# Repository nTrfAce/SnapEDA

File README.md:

# SnapEDA

See also https://oshpark.com/profiles/nTrfAce for links to order the boards, images of them, and suggestions on connector part numbers.

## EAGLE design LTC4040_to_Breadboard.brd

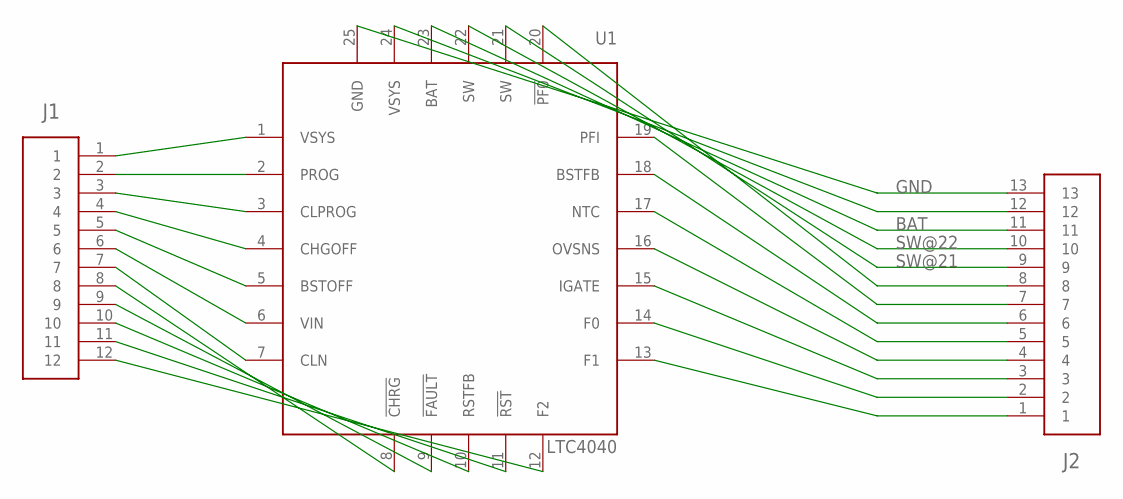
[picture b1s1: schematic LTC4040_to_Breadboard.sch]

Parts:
J1: CONNECTOR_12; 68000-112HLF
J2: CONNECTOR_13; 68000-113HLF_NO_SQUARE
U1: LTC4040; QFN50P500X400X80-25N

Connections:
BAT: J2.11, U1.23 (BAT)
GND: J2.13, U1.25 (GND)
unnamed: J1.1, U1.1 (VSYS)
unnamed: J1.2, U1.2 (PROG)
unnamed: J1.3, U1.3 (CLPROG)
unnamed: J1.4, U1.4 (CHGOFF)
unnamed: J1.5, U1.5 (BSTOFF)
unnamed: J1.6, U1.6 (VIN)
unnamed: J1.7, U1.7 (CLN)
unnamed: J1.8, U1.8 (!CHRG)
unnamed: J1.9, U1.9 (!FAULT)
unnamed: J1.10, U1.10 (RSTFB)
unnamed: J1.11, U1.11 (!RST)
unnamed: J1.12, U1.12 (F2)
unnamed: J2.1, U1.13 (F1)
unnamed: J2.2, U1.14 (F0)
unnamed: J2.3, U1.15 (IGATE)
unnamed: J2.4, U1.16 (OVSNS)
unnamed: J2.5, U1.17 (NTC)
unnamed: J2.6, U1.18 (BSTFB)
unnamed: J2.7, U1.19 (PFI)
unnamed: J2.8, U1.20 (!PF0)
unnamed: J2.12, U1.24 (VSYS)
SW@21: J2.9, U1.21 (SW)
SW@22: J2.10, U1.22 (SW)

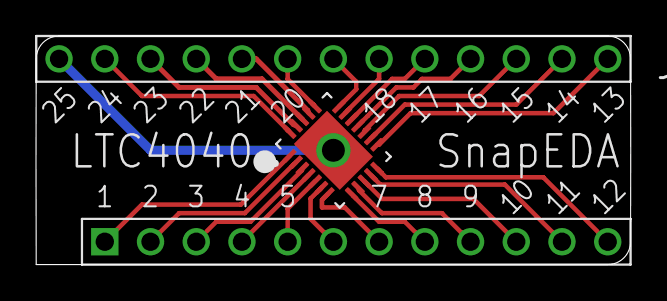
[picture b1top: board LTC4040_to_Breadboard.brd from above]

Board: 2 copper layers, 33.0 x 12.7 mm, 3 parts (0 on the bottom side), 25 nets.

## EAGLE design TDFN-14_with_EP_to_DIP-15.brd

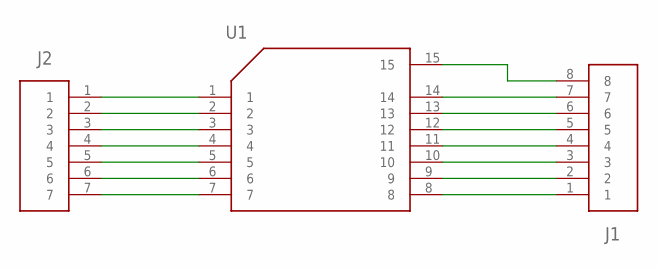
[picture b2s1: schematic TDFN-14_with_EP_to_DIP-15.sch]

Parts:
J1: CONNECTOR_8-NO_SQUARE; 68000-108HLF-NO-SQUARE
J2: CONNECTOR_7; 68000-107HLF
U1: IC_GENERIC_14_PLUS_EP-DFN-14_PLUS_EP; SON40P300X300X75-14N

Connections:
unnamed: J1.1, U1.8
unnamed: J1.2, U1.9
unnamed: J1.3, U1.10
unnamed: J1.4, U1.11
unnamed: J1.5, U1.12
unnamed: J1.6, U1.13
unnamed: J1.7, U1.14
unnamed: J1.8, U1.15
unnamed: J2.1, U1.1
unnamed: J2.2, U1.2
unnamed: J2.3, U1.3
unnamed: J2.4, U1.4
unnamed: J2.5, U1.5
unnamed: J2.6, U1.6
unnamed: J2.7, U1.7

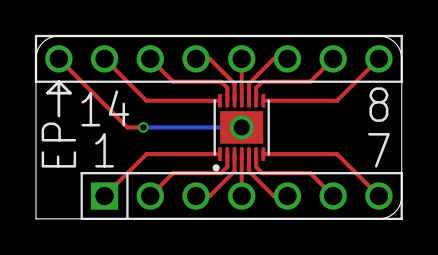
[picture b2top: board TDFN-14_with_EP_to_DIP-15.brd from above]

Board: 2 copper layers, 20.3 x 10.2 mm, 3 parts (0 on the bottom side), 15 nets.

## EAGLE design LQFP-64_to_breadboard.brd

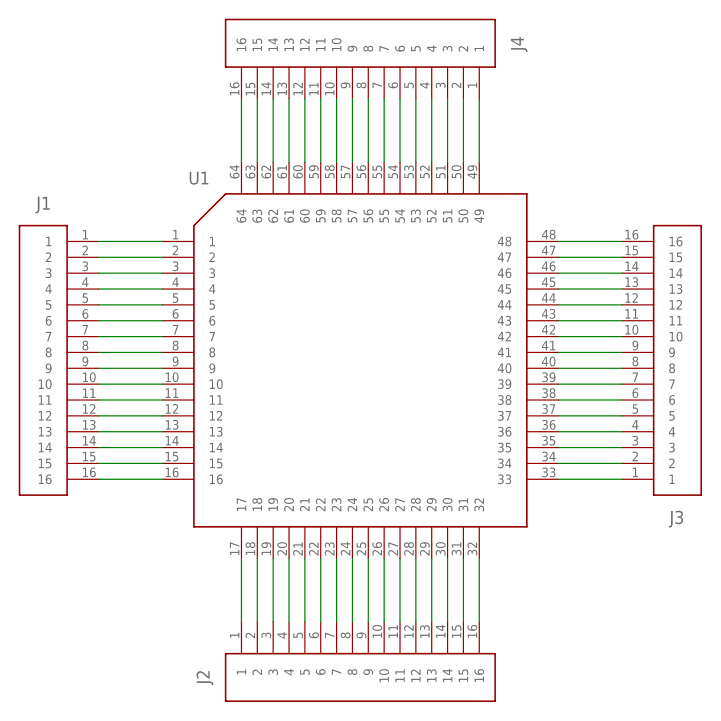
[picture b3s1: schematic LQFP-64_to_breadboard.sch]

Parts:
J1: CONNECTOR_16; 68000-116HLF
J2, J3, J4: CONNECTOR_16-NO_SQUARE; 68000-116HLF-NO-SQUARE
U1: IC_GENERIC_64-LQFP; QFP50P1200X1200X160-64N

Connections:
unnamed: J1.1, U1.1
unnamed: J1.2, U1.2
unnamed: J1.3, U1.3
unnamed: J1.4, U1.4
unnamed: J1.5, U1.5
unnamed: J1.6, U1.6
unnamed: J1.7, U1.7
unnamed: J1.8, U1.8
unnamed: J1.9, U1.9
unnamed: J1.10, U1.10
unnamed: J1.11, U1.11
unnamed: J1.12, U1.12
unnamed: J1.13, U1.13
unnamed: J1.14, U1.14
unnamed: J1.15, U1.15
unnamed: J1.16, U1.16
unnamed: J2.1, U1.17
unnamed: J2.2, U1.18
unnamed: J2.3, U1.19
unnamed: J2.4, U1.20
unnamed: J2.5, U1.21
unnamed: J2.6, U1.22
unnamed: J2.7, U1.23
unnamed: J2.8, U1.24
unnamed: J2.9, U1.25
unnamed: J2.10, U1.26
unnamed: J2.11, U1.27
unnamed: J2.12, U1.28
unnamed: J2.13, U1.29
unnamed: J2.14, U1.30
unnamed: J2.15, U1.31
unnamed: J2.16, U1.32
unnamed: J3.1, U1.33
unnamed: J3.2, U1.34
unnamed: J3.3, U1.35
unnamed: J3.4, U1.36
unnamed: J3.5, U1.37
unnamed: J3.6, U1.38
unnamed: J3.7, U1.39
unnamed: J3.8, U1.40
unnamed: J3.9, U1.41
unnamed: J3.10, U1.42
unnamed: J3.11, U1.43
unnamed: J3.12, U1.44
unnamed: J3.13, U1.45
unnamed: J3.14, U1.46
unnamed: J3.15, U1.47
unnamed: J3.16, U1.48
unnamed: J4.1, U1.49
unnamed: J4.2, U1.50
unnamed: J4.3, U1.51
unnamed: J4.4, U1.52
unnamed: J4.5, U1.53
unnamed: J4.6, U1.54
unnamed: J4.7, U1.55
unnamed: J4.8, U1.56
unnamed: J4.9, U1.57
unnamed: J4.10, U1.58
unnamed: J4.11, U1.59
unnamed: J4.12, U1.60
unnamed: J4.13, U1.61
unnamed: J4.14, U1.62
unnamed: J4.15, U1.63
unnamed: J4.16, U1.64

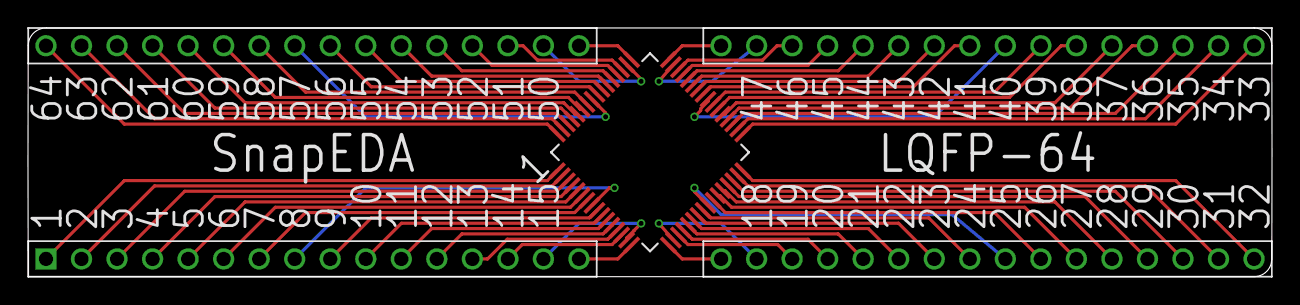
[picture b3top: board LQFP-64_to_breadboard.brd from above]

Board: 2 copper layers, 88.9 x 17.8 mm, 5 parts (0 on the bottom side), 64 nets.

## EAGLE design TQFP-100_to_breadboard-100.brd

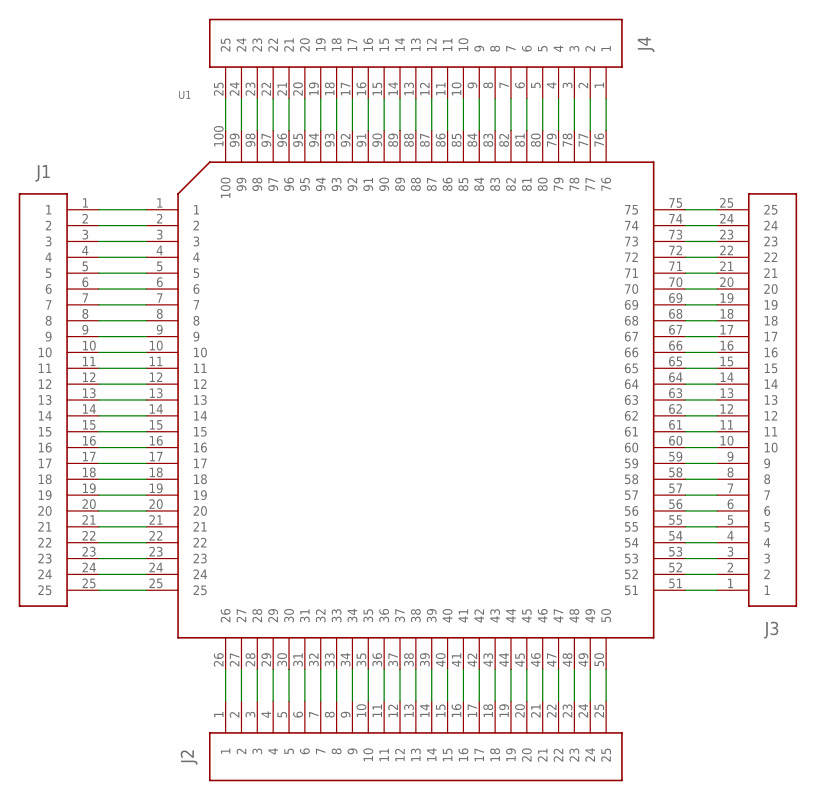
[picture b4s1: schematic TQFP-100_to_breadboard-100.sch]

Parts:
J1: CONNECTOR_25; 68000-125HLF
J2, J3, J4: CONNECTOR_25_NO_SQUARE; 68000-125HLF_NO_SQUARE
U1: IC-GENERIC-100-TQFP; QFP40P1400X1400X120-100N

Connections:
unnamed: J1.1, U1.1
unnamed: J1.2, U1.2
unnamed: J1.3, U1.3
unnamed: J1.4, U1.4
unnamed: J1.5, U1.5
unnamed: J1.6, U1.6
unnamed: J1.7, U1.7
unnamed: J1.8, U1.8
unnamed: J1.9, U1.9
unnamed: J1.10, U1.10
unnamed: J1.11, U1.11
unnamed: J1.12, U1.12
unnamed: J1.13, U1.13
unnamed: J1.14, U1.14
unnamed: J1.15, U1.15
unnamed: J1.16, U1.16
unnamed: J1.17, U1.17
unnamed: J1.18, U1.18
unnamed: J1.19, U1.19
unnamed: J1.20, U1.20
unnamed: J1.21, U1.21
unnamed: J1.22, U1.22
unnamed: J1.23, U1.23
unnamed: J1.24, U1.24
unnamed: J1.25, U1.25
unnamed: J2.1, U1.26
unnamed: J2.2, U1.27
unnamed: J2.3, U1.28
unnamed: J2.4, U1.29
unnamed: J2.5, U1.30
unnamed: J2.6, U1.31
unnamed: J2.7, U1.32
unnamed: J2.8, U1.33
unnamed: J2.9, U1.34
unnamed: J2.10, U1.35
unnamed: J2.11, U1.36
unnamed: J2.12, U1.37
unnamed: J2.13, U1.38
unnamed: J2.14, U1.39
unnamed: J2.15, U1.40
unnamed: J2.16, U1.41
unnamed: J2.17, U1.42
unnamed: J2.18, U1.43
unnamed: J2.19, U1.44
unnamed: J2.20, U1.45
unnamed: J2.21, U1.46
unnamed: J2.22, U1.47
unnamed: J2.23, U1.48
unnamed: J2.24, U1.49
unnamed: J2.25, U1.50
unnamed: J3.1, U1.51
unnamed: J3.2, U1.52
unnamed: J3.3, U1.53
unnamed: J3.4, U1.54
unnamed: J3.5, U1.55
unnamed: J3.6, U1.56
unnamed: J3.7, U1.57
unnamed: J3.8, U1.58
unnamed: J3.9, U1.59
unnamed: J3.10, U1.60
unnamed: J3.11, U1.61
unnamed: J3.12, U1.62
unnamed: J3.13, U1.63
unnamed: J3.14, U1.64
unnamed: J3.15, U1.65
unnamed: J3.16, U1.66
unnamed: J3.17, U1.67
unnamed: J3.18, U1.68
unnamed: J3.19, U1.69
unnamed: J3.20, U1.70
unnamed: J3.21, U1.71
unnamed: J3.22, U1.72
unnamed: J3.23, U1.73
unnamed: J3.24, U1.74
unnamed: J3.25, U1.75
unnamed: J4.1, U1.76
unnamed: J4.2, U1.77
unnamed: J4.3, U1.78
unnamed: J4.4, U1.79
unnamed: J4.5, U1.80
unnamed: J4.6, U1.81
unnamed: J4.7, U1.82
unnamed: J4.8, U1.83
unnamed: J4.9, U1.84
unnamed: J4.10, U1.85
unnamed: J4.11, U1.86
unnamed: J4.12, U1.87
unnamed: J4.13, U1.88
unnamed: J4.14, U1.89
unnamed: J4.15, U1.90
unnamed: J4.16, U1.91
unnamed: J4.17, U1.92
unnamed: J4.18, U1.93
unnamed: J4.19, U1.94
unnamed: J4.20, U1.95
unnamed: J4.21, U1.96
unnamed: J4.22, U1.97
unnamed: J4.23, U1.98
unnamed: J4.24, U1.99
unnamed: J4.25, U1.100

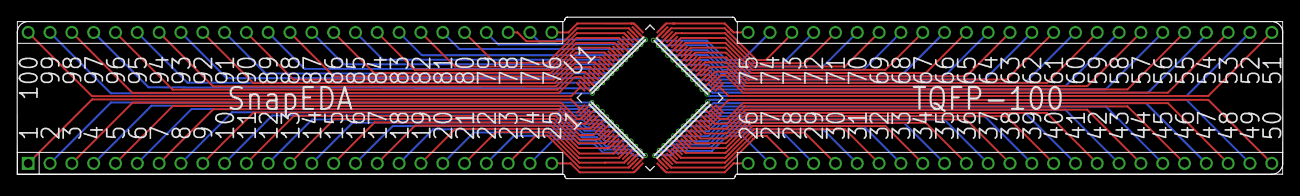
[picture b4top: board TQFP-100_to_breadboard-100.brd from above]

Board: 2 copper layers, 147.4 x 18.8 mm, 5 parts (0 on the bottom side), 100 nets.

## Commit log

2018-04-02 Initial commit. SOIC-8-N to DIP-8 breakout, MIT license, SnapEDA library.
2018-04-02 Added PDF of SOIC-8-N breakout.
2018-04-02 Updated last saved time of SOIC-8-N schematic.
2018-04-03 Added QFN-16 QFN65P400X400X80-17N to DIP-16+1. For example for the Maxim Integrated DS28E17.
2018-04-03 Rerouted QFN-16 PCB. Thicker traces, board outline changed to 0 width.
2018-04-03 Moved silkscreen text so vias don't interfere.
2018-04-03 added PDF of QFN-16.
2018-04-04 Added TQFP-32 breakout to DIP-32-0.600, for example for the ATmega328P.
2018-04-04 Fixed text on the bottom of TQFP-32 breakout.
2018-04-05 Added TQFN-100 breakout, in progress.
2018-04-05 continuing work on the TQFP-100 routing.
2018-04-06 continuing routing traces.
2018-04-07 finished TQFP-100
2018-04-07 added TQFP-100 schematic PDF. Added example IC P/N ATMEGA2560V-8AU to text on schematic.
2018-04-07 Added QFN-24 (without Exposed Pad) to DIP-24-0.300.
2018-04-07 added a link to OSH Park to the readme.
2018-04-08 Added LQFP-64 to breadboard breakout.
2018-04-10 Added SOT-23-6 board.
2018-04-10 Added SOT-23-5 breakout.
2018-04-11 Added SOT-143 to breadboard breakout. Four pin package similar to an SOT-23.
2018-04-12 Added SOT-23(-3) to breadboard.
2018-04-13 fixed SOT-143 board - previous version was 0.200" wide, and OSH Park requires boards to be 0.250" or more on X and Y dimensions. So it has a vestigal PCB extension of 0.050" on the right side.
2018-04-15 Added breakout for TDFN-14 with Exposed Pad to DIP-14+1-0.300.
2019-03-02 Add breakout for LTC4040 Orderable at https://oshpark.com/shared_projects/wdSY3owb
    Breakout from an Analog Devices/Linear Technology LTC4040 “2.5A Battery Backup Power Manager” IC. Boost SMPS with 5V out, and buck SMPS to charge lithium cell. Li-Ion selectable 3.95V/4.0V/4.05V/4.1V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
    https://www.analog.com/en/products/ltc4040.html
    https://www.analog.com/media/en/technical-documentation/data-sheets/4040fb.pdf
    Package UFD, QFN 4mm x 5mm. 24 pins plus Exposed Pad. LTC4040EUFD
